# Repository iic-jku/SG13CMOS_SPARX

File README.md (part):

# SPARX: An Open-Source, Automated, Programmatically Generated, Frequency-Scalable Six-Port Receiver in 130-nm CMOS

(c) 2025-2026 Simon Dorrer, David Kellerer-Pirklbauer, and Harald Pretl

Institute for Integrated Circuits and Quantum Computing, Johannes Kepler University (JKU), Linz, Austria

> [!IMPORTANT]
> This repository requires the [IIC-OSIC-TOOLS](https://github.com/iic-jku/IIC-OSIC-TOOLS) container with tag `2026.11` or later.

> [!TIP]
> This repository is based on the [ihp-sg13g2-ams-chip-template](https://github.com/iic-jku/ihp-sg13g2-ams-chip-template) template repository and has been extended with electromagnetic (EM) simulations using the tool AWS Palace. For a better understanding of the folder structure, how to use the Makefiles, and how to implement your own designs, it is recommended to go through this [tutorial](https://iic-jku.github.io/ihp-sg13g2-ams-chip-template/index.html).

> [!NOTE]
> SPARX stands for **S**ix-**P**ort **A**utomated Receiver (**RX**). The name also carries a subtle double meaning: *SPARX* sounds like *spark*, which translates to *Funken* in German. Fittingly, the German verb *funken* also means to communicate via radio, a subtle nod to the wireless world this receiver was designed for.

<p align="center">
  
  <br>
  <em>Die photo of the ihp-sg13cmos six-port receiver for 160 GHz (1 × 1.4 mm²), taped out in March 2026.</em>
</p>

<p align="center">
  
  <br>
  <em>Chip render of the ihp-sg13cmos six-port receiver for 160 GHz with M5 GND plane and pinout (1 × 1.4 mm²).</em>
</p>

## Chip Specifications

| Parameter           | Value                                                                             |
| ------------------- | --------------------------------------------------------------------------------- |
| Technology          | IHP SG13CMOS (130 nm CMOS)                                                        |
| Die Area            | 1 × 1.4 mm²                                                                       |
| Supply Voltage      | 1.5 V                                                                             |

## Documentation

> [!IMPORTANT]
> This work has been published at the 2026 IEEE Nordic Circuits and Systems Conference (NorCAS) and is available in [IEEE Xplore](https://ieeexplore.ieee.org/document/11791174), doi: [10.1109/NorCAS71164.2026.11791174](https://doi.org/10.1109/NorCAS71164.2026.11791174). The preprint is available on [ResearchGate](https://www.researchgate.net/publication/418259168_SPARX_An_Open-Source_Automated_Programmatically_Generated_Frequency-Scalable_Six-Port_Receiver_in_130-nm_CMOS). [Cite This Work](#cite-this-work) gives the BibTeX entries.
>
> © 2026 IEEE. Personal use of this material is permitted. Permission from IEEE must be obtained for all other uses, in any current or future media, including reprinting/republishing this material for advertising or promotional purposes, creating new collective works, for resale or redistribution to servers or lists, or reuse of any copyrighted component of this work in other works.

The full documentation of SPARX is available [here](https://iic-jku.github.io/SG13CMOS_SPARX/index.html).

## Overview

The complete layout is generated in Python using self-made RF devices as a GDSFactory IHP PDK add-on. S-parameter simulation of the passive RF structures (BPF, WPD, and BLC) is performed with AWS Palace. The de-embedded EM results are then fitted to passivity-enforced lumped element models with [snp2le](https://github.com/iic-jku/snp2le), in both SPICE and Spectre dialects, and resimulated in Xschem testbenches with ngspice and VACASK. The six-port core is verified in two ways: as a single fitted model of the full-core EM simulation and as a composition of the individual BPF, WPD, and BLC models. With KLayout, Magic, and Netgen, a complete DRC, LVS, and PEX verification flow is implemented, and gdscheck adds a third DRC engine. The SBD-based power detector is designed in Xschem and simulated with ngspice and VACASK. This repository is controlled by a Makefile. Just clone it and run `make all` to build the six-port receiver at 160 GHz, verify it, run the EM simulations, extract the lumped element models, and simulate all testbenches. To generate a frequency-scalable layout at a different target frequency, for example 77 GHz, run `make build-layout FREQ=77`. A [regression](#regression) on every push to `main` exercises the complete tool flow in GitHub Actions inside the IIC-OSIC-TOOLS container. The following video demonstrates the generation of six-port receivers from 60 GHz to 300 GHz in under one minute.

**Index Terms:** Branch-line coupler, frequency-scalable layout, GDSFactory, hairpin coupled-line bandpass filter, IHP Open-PDK, mmWave, open-source EDA, power detector, programmatic layout, Schottky barrier diode, six-port receiver, Wilkinson power divider.

https://github.com/user-attachments/assets/a1e6cacb-4a70-4f2c-9b7a-f4b6fbb5a47a
<p align="center">
  <em>Generation of Six-Port Receivers from 60 GHz to 300 GHz.</em>
</p>

## References
To understand the principle of six-port receivers and their architectures, it is recommended to read the following references:
- A. Koelpin, G. Vinci, B. Laemmle, D. Kissinger and R. Weigel, "The Six-Port in Modern Society," in IEEE Microwave Magazine, vol. 11, no. 7, pp. 35-43, Dec. 2010, doi: 10.1109/MMM.2010.938584: https://ieeexplore.ieee.org/document/5590352
- T. Hentschel, "The six-port as a communications receiver," in IEEE Transactions on Microwave Theory and Techniques, vol. 53, no. 3, pp. 1039-1047, March 2005, doi: 10.1109/TMTT.2005.843507: https://ieeexplore.ieee.org/document/1406309
- M. Mailand, "System Analysis of Six-Port-Based RF-Receivers," in IEEE Transactions on Circuits and Systems I: Regular Papers, vol. 65, no. 1, pp. 319-330, Jan. 2018, doi: 10.1109/TCSI.2017.2734922: https://ieeexplore.ieee.org/document/8011483

## Requirements

To build this six-port receiver, the following tools and their respective dependencies are required:
- GDSFactory: https://github.com/gdsfactory/gdsfactory
- IHP Open-PDK GDSFactory Addon: https://github.com/iic-jku/IHP-GDSFactory-Addon
- IHP Open-PDK: https://github.com/iic-jku/IHP-Open-PDK
- snp2le (S-parameter to lumped element netlist conversion): https://github.com/iic-jku/snp2le, available on PyPI: https://pypi.org/project/snp2le/

GDSFactory, the IHP Open-PDK, and snp2le are already installed in the IIC-OSIC-TOOLS container.

The updated IHP Open-PDK GDSFactory version contains all self-made RF devices and wraps existing PCells provided by the IHP Open-PDK, allowing them to be used directly within the GDSFactory framework. We choose this approach because it requires very little maintenance. If IHP changes the layout of a cell, no wrapper update is necessary. Only interface changes to a PCell function require updates on our side.

## Block Diagram
- Six-Port
  - Branch Line Coupler (BLC)
  - Wilkinson Power Divider (WPD)
  - Hairpin Coupled-Line Bandpass Filter (BPF)
- Power Detector (PD)
  - Schottky Barrier Diode (SBD)
- Metal Stack
  - TopMetal2 (TM2): RF traces
  - Metal5 (M5): GND plane

<p align="center">
  
  <br>
  <em>Block diagram of the six-port receiver.</em>
</p>

## Schematic of SBD-based Power Detector

<p align="center">
  
  <br>
  <em>Schematic of the SBD-based power detector with replica circuit for fully-differential measurements. The supply and bias voltages are decoupled on-chip by MIM capacitors. The filtering capacitor is placed off-chip.</em>
</p>

## Design Flow

An overview of the open-source design flow for SPARX is shown below. The flow covers schematic entry, circuit simulation, parameterized layout generation, physical verification, post-layout simulation, EM simulation and resimulation of fitted lumped element models. All required tools and the IHP Open-PDK run inside the IIC-OSIC-TOOLS Docker image. The complete design flow is automated with Makefile targets, which are explained below.

<p align="center">
  
  <br>
  <em>Overview of the open-source design flow for SPARX.</em>
</p>

## Directory Structure

<details>
<summary>Show Directory Structure</summary>

```text
📁 SG13CMOS_SPARX/
├─ 📁 .github/
│  └─ 📁 workflows/
│     ├─ license-check.yml
│     ├─ quarto-publish.yml
│     └─ regression.yml
├─ 📁 doc/
│  ├─ 📁 fig/
│  ├─ 📁 videos/
│  ├─ _quarto.yml
│  ├─ index.qmd
│  ├─ requirements.txt
│  └─ Makefile
├─ 📁 LICENSES/
│  ├─ Apache-2.0.txt
│  └─ SHL-2.1.txt
├─ 📁 layout/
│  ├─ sparx60_top.gds
│  ├─ ...
│  ├─ sparx160_top.gds
│  ├─ ...
│  ├─ sparx300_top.gds
│  └─ sparx_powdet_sbd.gds
├─ 📁 measurements/
├─ 📁 netlist/
│  ├─ 📁 layout/
│  │  ├─ sparx_powdet_sbd_klayout.cir
│  │  └─ sparx_powdet_sbd_magic.ext.spc
│  ├─ 📁 pex/
│  │  ├─ sparx_powdet_sbd_klayout_pex_3.spice
│  │  └─ sparx_powdet_sbd_magic_pex_3.spice
│  ├─ 📁 schematic/
│  │  ├─ sparx_powdet_sbd_klayout.cdl
│  │  └─ sparx_powdet_sbd_magic.spice
│  ├─ 📁 spectre/
│  │  ├─ sparx_blc_le.inc
│  │  ├─ sparx_bpf_le.inc
│  │  ├─ sparx_core_le.inc
│  │  └─ sparx_wpd_le.inc
│  └─ 📁 spice/
│     ├─ sparx_blc_le.spice
│     ├─ sparx_bpf_le.spice
│     ├─ sparx_core_le.spice
│     └─ sparx_wpd_le.spice
├─ 📁 release/
│  ├─ 📁 v.1.0.0/
│  │  ├─ 📁 gds/
│  │  ├─ 📁 img/
│  │  └─ ReleaseNote.md
│  └─ 📁 v.2.0.0/
│     ├─ 📁 gds/
│     ├─ 📁 img/
│     └─ 📁 netlist/
├─ 📁 render/
│  ├─ 📁 blender/
│  └─ 📁 img/
│     ├─ sparx160_top_black.png
│     ├─ sparx160_top_black_TM2.png
│     └─ sparx160_top_white.png
├─ 📁 schematic/
│  └─ 📁 xschem/
│     ├─ sparx_blc_le.sym
│     ├─ sparx_bpf_le.sym
│     ├─ sparx_core.sch
│     ├─ sparx_core.sym
│     ├─ sparx_core_le.sym
│     ├─ sparx_powdet_sbd.sch
│     ├─ sparx_powdet_sbd.sym
│     ├─ sparx_powdet_sbd_pex.sym
│     ├─ sparx_top.sch
│     ├─ sparx_top.sym
│     ├─ sparx_top_le.sch
│     ├─ sparx_top_le.sym
│     ├─ sparx_top_lvs.sch
│     ├─ sparx_wpd_le.sym
│     └─ xschemrc
├─ 📁 scripts/
│  ├─ 📁 assets/
│  ├─ check_pex_ports.py
│  ├─ img2lay.py
│  ├─ prune_pex_symbol.py
│  ├─ six_port_gen.py
│  └─ sparx_powdet_sbd_circuit.ipynb
├─ 📁 sscs-ose-code-a-chip/
│  ├─ 📁 assets/
│  ├─ README.md
│  └─ SPARX_JKU_ISSCC2027.ipynb
├─ 📁 testbenches/
│  └─ 📁 xschem/
│     ├─ 📁 plot_simulations/
│     │  ├─ 📁 data/
│     │  ├─ 📁 figures/
│     │  ├─ check_sparx_powdet_sbd_tb_acsp_ngspice.py
│     │  ├─ ngspice2python.py
│     │  ├─ plot_n_port_tb_acsp_ngspice.py
│     │  ├─ plot_n_port_tb_acsp_vacask.py
│     │  ├─ plot_n_port_tb_tran_ngspice.py
│     │  ├─ plot_sparx_powdet_sbd_tb_hb_V-W_vacask.py
│     │  ├─ plot_sparx_powdet_sbd_tb_hb_dBV-dBV_vacask.py
│     │  ├─ plot_sparx_powdet_sbd_tb_nf_vacask.py
│     │  ├─ plot_sparx_powdet_sbd_tb_pss_vacask.py
│     │  ├─ plot_sparx_powdet_sbd_tb_tn_lo_vacask.py
│     │  ├─ plot_sparx_powdet_sbd_tb_tn_vacask.py
│     │  ├─ plot_sparx_top_le_tb_nf_vacask.py
│     │  ├─ plot_sparx_top_le_tb_rx_vacask.py
│     │  ├─ plot_sparx_top_le_tb_tn_vacask.py
│     │  └─ sparam_plot.py
│     ├─ sparx_blc_le_tb_acsp_ngspice.sch
│     ├─ ...
│     ├─ sparx_core_tb_acsp_ngspice.sch
│     ├─ ...
│     ├─ sparx_powdet_sbd_tb_acsp_ngspice.sch
│     ├─ ...
│     ├─ sparx_powdet_sbd_tb_ngspice.sch
│     ├─ ...
│     ├─ sparx_top_le_tb_nf_vacask.sch
│     ├─ sparx_top_le_tb_rx_vacask.sch
│     ├─ sparx_top_le_tb_tn_vacask.sch
│     ├─ sparx_top_le_tb_tran_ngspice.sch
│     ├─ sparx_top_tb_tran_ngspice.sch
│     ├─ sim_range.inc
│     ├─ sim_range.spice
│     └─ xschemrc
├─ 📁 verification/
│  ├─ 📁 drc/
│  │  ├─ 📁 sparx160_top.klayout.drc/
│  │  ├─ 📁 sparx160_top.magic.drc/
│  │  ├─ 📁 sparx_powdet_sbd.klayout.drc/
│  │  └─ 📁 sparx_powdet_sbd.magic.drc/
│  ├─ 📁 em/
│  │  ├─ 📁 layout/
│  │  ├─ 📁 metal_model/
│  │  ├─ 📁 palace_model/
│  │  ├─ 📁 s-parameter/
│  │  ├─ 📁 scripts/
│  │  └─ 📁 stackups/
│  └─ 📁 lvs/
│     ├─ 📁 sparx_powdet_sbd.klayout.lvs/
│     └─ 📁 sparx_powdet_sbd.magic.lvs/
├─ .gitattributes
├─ .gitignore
├─ CITATION.cff
├─ KNOWN_ISSUES.md
├─ LICENSE
├─ Makefile
├─ README.md
└─ REUSE.toml
```

</details>

## Xschem Configuration

Xschem reads exactly one `xschemrc` at start-up, and that file decides which symbol libraries are visible and where netlists and simulation output are written. This repository ships one per folder that holds schematics:

| `xschemrc` | Belongs to |
| --- | --- |
| [`schematic/xschem/xschemrc`](schematic/xschem/xschemrc) | the six-port and power detector schematics and symbols |
| [`testbenches/xschem/xschemrc`](testbenches/xschem/xschemrc) | the ngspice and VACASK testbenches |

### What Every File Does

Both run the same four steps, in this order:

1. **Pick the PDK.** `PDK_ROOT` is probed in the usual install locations if the environment does not set it, and `PDK` falls back to `ihp-sg13g2`. The container already exports `PDK_ROOT`, and [`.designinit`](.designinit) exports `PDK`, so this step is only a safety net for an Xschem started outside that environment.
2. **Source the PDK `xschemrc`.** `$PDK_ROOT/$PDK/libs.tech/xschem/xschemrc` brings in the IHP device symbols, the ngspice and VACASK model paths and the IHP menu. It is guarded by `[info exists PDK]` so it is read once even when the two project files are chained.
3. **Add the project library paths.** `append_xschem_library_path_unique` appends a folder to `XSCHEM_LIBRARY_PATH` only if it is not already there, so the same folder never appears twice no matter how the files are chained. [`schematic/xschem/xschemrc`](schematic/xschem/xschemrc) puts itself and `testbenches/xschem/` on the path. [`testbenches/xschem/xschemrc`](testbenches/xschem/xschemrc) adds none of its own and gets both from the file it sources.
4. **Pin the netlist directory.** `pin_netlist_dir` decides where `xschem netlist` and the simulators write.

Both helper procedures are defined behind an `[info commands ...]` guard, so sourcing one file from the other is harmless and the order does not matter.

### How the Files Are Chained

The testbench file pulls in the schematic file:

```text
testbenches/xschem/xschemrc
└─ source schematic/xschem/xschemrc
```

Either file therefore sees both folders, which is what lets a testbench instantiate `sparx_powdet_sbd.sym` or one of the `sparx_*_le.sym` lumped element symbols, and what lets you open a testbench from a session started in `schematic/xschem/`.

### Where Netlists and Simulation Output Go

`pin_netlist_dir` maps the folder of the schematic being netlisted to a `simulations/` folder:

| Schematic lives in | `netlist_dir` |
| --- | --- |
| `testbenches/xschem` | `testbenches/xschem/simulations` |
| `schematic/xschem` | `testbenches/xschem/simulations` |
| anywhere else (a PDK example) | left at the value the `xschemrc` pinned |

It runs twice: once while the `xschemrc` is read, using that file's own folder, and again through Xschem's `load_file_postprocess` hook for every schematic that is opened afterwards. The second call keeps the netlist next to its own schematic tree no matter where the session was started, so the relative includes of the testbenches, such as `.include ../../../netlist/spice/sparx_bpf_le.spice` or `.include ../../../netlist/pex/sparx_powdet_sbd_magic_pex_3.spice`, always resolve from `testbenches/xschem/simulations/`.

A `set netlist_dir` passed on the Xschem command line still wins, because `--command` runs after the file is loaded. The LVS netlist targets rely on this to write into `netlist/schematic/`, and `sim-xschem` to write into `testbenches/xschem/simulations/`.

Both `simulations/` folders are generated and git-ignored.

### Which File Is Used

- The Makefile targets always name one explicitly with `--rcfile`, so a target behaves the same from any working directory.
- Starting Xschem from within one of the two folders picks up that folder's file, which is the normal interactive case.
- `make open` starts Xschem in the file's own directory, so the same rule applies to every button of the file browser, see [Open the Design Files](#open-the-design-files).

## Makefile Structure

The whole flow is driven by the single top-level `Makefile`, and [Makefile Targets](#makefile-targets) below documents each target. The figure below shows how the targets are connected when you run `make all`.

<p align="center">
  
  <br>
  <em>Overview of the Makefile targets.</em>
</p>

Every coloured branch is one stage of the flow, and its header names the folders the stage writes to. The numbers in the headers give the execution order of `make all`, and inside a branch the targets run from top to bottom.

All targets live in the one `Makefile`, so every arrow is a direct `$(MAKE) <target>` call. The boxes directly below a header are called by `make all` itself, and an indented box is called by the nearest box above it with less indent. A box with a thicker border calls the boxes indented below it. The second line of a box shows the parameters of the call, where `*` stands for any part of a testbench name, and in `sparx*_top` for the design frequency. A box marked ×N stands for N calls of the same target, for example one SPICE and one Spectre fit per `snp2le` box, and a box that names two targets calls each of them once. The dashed boxes with a `WITH_CORE=1` tag run only with `make all WITH_CORE=1`, see below. The figure leaves out the helper steps. `copy-sparam` copies the Touchstone files of each EM run to `verification/em/s-parameter/`, `klayout-lvs` and `magic-lvs` first export the schematic netlist with `klayout-lvs-netlist` and `magic-lvs-netlist`, and `klayout-pex` and `magic-pex` first regenerate the PEX symbol with `symbol-pex`.

At the top level, `make all` runs five stages in this order:

1. **Layout**: `build-top` installs the GDSFactory PDK add-on (`build-pdk`), generates the 160 GHz layout together with the EM structures in `verification/em/layout/` (`build-layout`), and renders the top-level GDS (`render-gds`).
2. **Verification**: `klayout-verify` runs DRC, LVS and PEX of the SBD power detector `sparx_powdet_sbd`, `gdscheck-drc` its gdscheck DRC, and `magic-verify` its LVS and PEX. Then `klayout-drc` and `gdscheck-drc` (both `DRC_LEVEL=macro`) check the top cell of the design frequency, `sparx160_top` by default and `sparx<FREQ>_top` with `FREQ=<GHz>`. The figure already shows the LVS of the top cell (`klayout-lvs`, `magic-lvs`), which `make all` does not run yet: it follows once top-level LVS works, see [`ToDo.md`](ToDo.md).
3. **EM simulation**: AWS Palace solves the BPF, WPD and BLC (`sim-bpf-em`, `sim-wpd-em`, `sim-blc-em`), and `copy-sparam` copies the raw and de-embedded Touchstone files of each run to `verification/em/s-parameter/`.
4. **LE models**: `snp2le` fits the raw Touchstone file of each block to a SPICE and a Spectre lumped element netlist, with the fit orders 13 (BPF), 10 (WPD) and 6 (BLC).
5. **Circuit simulation**: `sim-all` runs 22 of the 25 testbenches, all except the three transients of the passive LE models. With the power-detector design variants (`sim-powdet-variants`) and the post-layout runs of the receiver benches, these are 31 simulations.

The simulations run last, so the block benches and the composed-core benches use the LE models that the same invocation has just fitted.

The dashed boxes are the full six-port core: its EM solve (`sim-sparx-core-em`) and its fit with `ORDER=24` and the core's thermal noise (`LE_NOISE=thermal`). `make all` runs them only with `WITH_CORE=1`, because the seven-port EM solve takes about 20 times the core-hours of the three blocks, and the committed run needed 119 GB of memory on 128 MPI ranks. It runs them through `make sparx-core` as one step after the block fits. That step also copies the core's Touchstone files and runs the two `sparx_core_tb_acsp_*` benches, which `sim-all` then repeats. With the default `WITH_CORE=0`, `make all` simulates the committed full-core fit, `netlist/spice/sparx_core_le.spice` and `netlist/spectre/sparx_core_le.inc`, in the `sparx_core_le_tb_acsp_*` and `sparx_top_le_tb_*` benches.

> [!IMPORTANT]
> After a change to a structure parameter in `scripts/six_port_gen.py`, run `make sparx-core` or `make all WITH_CORE=1`. Otherwise the full-core benches (`sparx_core_le_tb_acsp_*`, `sparx_top_le_tb_*`) keep simulating the core fit of the old layout, and nothing warns about it.

`make regression` runs a short subset of these stages as a tool and flow smoke test, see [Regression](#regression).

## Makefile Targets

### Show Available Targets

The default Make target is `help`, so running `make` prints usage and all available targets with short descriptions.

```sh
make
make help
```

### PDK Guard

Every target except `help` and `clean` needs the `ihp-sg13g2` PDK. A wrong `$PDK`, for example `ihp-sg13cmos5l`, silently mixes technologies: DRC and LVS run against the wrong rule deck, Magic reads the wrong `magicrc`, `kpex` is handed the wrong `--pdk`, and the EM flow reads its process stackup from `$PDK_ROOT/$PDK/libs.tech/palace/`. The Makefile therefore compares `$PDK` against `REQUIRED_PDK` once when it is parsed, before any target runs:

```sh
$ sak-pdk ihp-sg13cmos5l
$ make klayout-drc
Makefile:25: *** PDK is "ihp-sg13cmos5l", but this chip needs "ihp-sg13g2". Run `sak-pdk ihp-sg13g2` in this shell and retry, or pass REQUIRED_PDK= to skip this check.  Stop.
```

The check is a parse-time conditional at the top of the Makefile, not a prerequisite of each target, so it costs nothing and cannot be forgotten when a target is added. `help` and `clean` are exempt, so the usage text and the cleanup still work under any PDK. `open` is not exempt: it launches Xschem, KLayout and Magic, which all read the selected PDK.

Switch the PDK with `sak-pdk ihp-sg13g2`, which also sets `PDKPATH`, `KLAYOUT_PATH`, `SPICE_USERINIT_DIR` and `STD_CELL_LIBRARY`. To run a single target against another PDK anyway, pass an empty `REQUIRED_PDK`:

```sh
make <target> REQUIRED_PDK=          # skip the check
make <target> REQUIRED_PDK=<pdk>     # require a different PDK
```

### Open the Design Files

Opens a file browser for this folder with `sak-open.py` from the [IIC-OSIC-TOOLS](https://github.com/iic-jku/IIC-OSIC-TOOLS), one button per design file, grouped by directory:

```sh
make open
```

All file types are ticked at startup, each checkbox showing how many files of that type the tree holds. `None` and `All` untick or tick every type at once, and `Rescan` rereads the tree immediately. The filter field keeps only the files whose path contains the typed text (case-insensitive), so `powdet` reduces the list to the files of the power detector and its testbenches. Clicking a directory heading folds it away. Hovering a button shows the file's size and age in the status line at the bottom. A right click on a button opens a menu with `Cell view` (all views of that cell, for example its `.sch`, `.sym` and `.gds`, wherever they live in the tree), `Scope here` (rescan from that file's directory), `Fold all`, `Save view` (remember the folded directories and ticked types for this tree), `Open shell` and `Copy path`.

Clicking a button launches the matching tool in the file's own directory, so Xschem finds its `simulations/` folder and KLayout the layouts where they belong:

| File type | Tool |
| --- | --- |
| `.sch`, `.sym` | Xschem |
| `.gds`, `.gds.gz`, `.oas`, `.oas.gz` | KLayout in edit mode |
| `.mag` | Magic |
| `.vcd`, `.fst`, `.gtkw` | GTKWave |
| `.raw` | gaw (ngspice rawfile) |
| `.png`, `.pdf` | the desktop's handler (`xdg-open`) |
| `.sv`, `.svh`, `.v`, `.vh`, `.vhd`, `.vhdl`, `.spice`, `.cir`, `.sp`, `.cdl`, `.sdc`, `.lef`, `.lib`, `.tcl`, `.mk`, `.yaml`, `.json`, `.py`, `.qmd`, `.tex`, `.md` and `Makefile` | gvim |

Only these types get a button. Files with any other extension (`.sh`, `.svg`, `.save`, `.inc`, `.sNp`, `.txt`, `.csv` and so on) are not listed.

Schematics and symbols that belong to one design unit share a single tabbed Xschem instance instead of one process per click. The unit is the nearest ancestor holding a `Makefile`, so the whole design is one unit and the documentation under [`doc/`](doc/) another. Every tab then writes its netlists to the folder the `xschemrc` pins, see [Xschem Configuration](#xschem-configuration).

The tree is rescanned every 15 s, so files a running flow produces appear on their own and are highlighted for a minute. Generated directories are skipped by default: `runs/`, `sim_build/`, `obj_dir/`, `simulations/`, `__pycache__/`, `_freeze/` and `.git/`. The Xschem `simulations/` folder is one of them, so the `.raw` files show up only with `--all`. Pass extra options with `OPEN_ARGS`:

```sh
make open OPEN_ARGS=--all                      # include the simulation outputs
make open OPEN_ARGS="--prune palace_model"     # skip one more directory name
```

At most 400 buttons are drawn at once, because each one is an X window, and what is left out is stated at the end of the list. That cap is easy to hit with `--all`, which also pulls in the Palace meshes under `verification/em/palace_model/` and every simulation output, so narrow it with `--prune` rather than scrolling. The same target exists in [`doc/`](doc/) for the documentation sources and figures.

> [!NOTE]
> This target needs a display. Run it inside the container's VNC/noVNC desktop or over X11 forwarding. In a shell-only container it stops with `cannot open a window`. The `.png` and `.pdf` buttons hand the file to the desktop's registered handler, so those two need the full VNC/noVNC session and do not work over a bare X forward.

### Build PDK

Clones and installs the GDSFactory PDK add-on (`IHP-GDSFactory-Addon`):

```sh
make build-pdk
```

### Build SPARX Layout

Generates the six-port layout GDS files for a specific frequency (e.g. `layout/sparx160_top.gds` and `layout/sparx_powdet_sbd.gds` for the default 160 GHz, or `layout/sparx77_top.gds` and `layout/sparx_powdet_sbd.gds` for 77 GHz) by calling `six_port_gen.py`:

```sh
make build-layout
make build-layout FREQ=77
make build-layout FREQ=77 NO_FILL=1
make build-layout FREQ=77 NO_FILL_M5=1
```

The `FREQ` parameter sets the design frequency in GHz (default: `160`). `NO_FILL=1` disables metal fill (faster for layout preview). `NO_FILL_M5=1` disables only the Metal5 ground fill.

> [!NOTE]
> `build-layout` also writes the EM sub-structures of the design (BLC, WPD, BPF, and the blank six-port core, each with the Palace port markers on layers 201..207) to `verification/em/layout/`. The EM simulation targets solve exactly these files, so the EM results always match the structures instantiated in the top-level layout.

### Build Frequency Sweep Automatically

Builds a frequency sweep by repeatedly calling `build-layout` for each frequency from `START_FREQ` to `STOP_FREQ` using `STEP_FREQ`.

```sh
make build-layout-sweep
make build-layout-sweep START_FREQ=60 STOP_FREQ=300 STEP_FREQ=20
make build-layout-sweep START_FREQ=60 STOP_FREQ=300 STEP_FREQ=20 NO_FILL=1
make build-layout-sweep START_FREQ=60 STOP_FREQ=300 STEP_FREQ=20 NO_FILL_M5=1
```

Default sweep settings are `START_FREQ=60`, `STOP_FREQ=300`, and `STEP_FREQ=20` (all in GHz). `NO_FILL` and `NO_FILL_M5` are forwarded to each `build-layout` run.

All thirteen layouts of the default sweep pass the KLayout DRC at `macro` level, and their EM simulations are clean as well. The repository commits the DRC reports, the EM results and the fitted models of 160 GHz only. Any other frequency reruns the same targets with `FREQ=<GHz>`, for example `make klayout-drc FREQ=80` and `make sim-bpf-em FREQ=80`.

### Build Top Cell

Builds the top-level cell by running `build-pdk`, `build-layout`, and `render-gds`:

```sh
make build-top
```

### Render Top Layout

Renders the top-level GDS `layout/sparx<FREQ>_top.gds` with `sak-render.py` from the [IIC-OSIC-TOOLS](https://github.com/iic-jku/IIC-OSIC-TOOLS):

```sh
make render-gds
make render-gds FREQ=77
```

Three images are written to the `render/img/` folder:

- `sparx<FREQ>_top_white.png` and `sparx<FREQ>_top_black.png`: all physical mask layers, on a white and on a black background.
- `sparx<FREQ>_top_black_TM2.png`: only `TopMetal2`, `TopVia2`, the `TopMetal2` filler and `Passiv` on a black background, which shows the six-port RF structures and the pads without the Metal5 ground plane underneath.

All three images are 2048 px wide and rendered with 4x oversampling. `sak-render.py` reads the layer colours from the PDK's own KLayout layer properties and crops to the drawn geometry, so the images have no border margin.

### Design Rule Check (DRC)

Runs DRC on the GDS layout in `layout/`. All three flows use `sak-drc.sh` and write their reports into per-cell run folders: `verification/drc/<CELL>.magic.drc/` (Magic), `verification/drc/<CELL>.klayout.drc/` (KLayout, `.lyrdb`) and `verification/drc/<CELL>.gdscheck.drc/` (gdscheck, `.lyrdb`). The run folders are wiped at the start of each run, so they always reflect the latest run only.

The `DRC_LEVEL` parameter selects the KLayout DRC level and the gdscheck suite (`sak-drc.sh -l`). It is ignored by `magic-drc`, since Magic has no selectable rule decks and always runs the full rule set compiled into the PDK's Magic tech file:

- `precheck` = the foundry precheck rule set and the pin checks (fast iteration)
- `macro` = block-in-isolation sign-off: the full FEOL and BEOL rules with off-grid, angle, recommended and pin checks, without chip-level density, the extra rules and antenna (default)
- `regular` = full-chip sign-off: all checks, including density, the extra rules and antenna

For the IHP Open-PDK, `sak-drc.sh` passes `--precheck_drc --no_density --no_offgrid --no_angle --disable_extra_rules --no_recommended` for `precheck`, `--no_density --disable_extra_rules` for `macro` and `--antenna` for `regular` to the PDK's `run_drc.py`, which adds the pin checks at every level:

| Check | `precheck` | `macro` _(default)_ | `regular` |
| --- | :---: | :---: | :---: |
| Foundry precheck rule set | ✓ | ✓ | ✓ |
| Pin / label | ✓ | ✓ | ✓ |
| Full FEOL + BEOL rules | – | ✓ | ✓ |
| Off-grid / angle | – | ✓ | ✓ |
| Recommended rules | – | ✓ | ✓ |
| Extra rules | – | – | ✓ |
| Density (full-chip fill) | – | – | ✓ |
| Antenna | – | – | ✓ |

The `DRC_JOBS` parameter (`sak-drc.sh -j`) sets how many jobs one run uses at most. The default is 4, or the CPU count if lower, for KLayout and every CPU the container may use for gdscheck, which runs as one process with that many threads. Up to 4 jobs, `precheck` and `macro` run as one KLayout process with that many threads, and `regular` runs its four rule sets (main, extra rules, density and antenna) as parallel processes and writes the reports of the last three into the subfolders `maximal/`, `density/` and `antenna/` of the run folder. Above 4, `run_drc.py` splits the rule deck into its tables, one process each, and merges their reports into one. Every KLayout process needs about 0.5 GiB of RAM plus the layout, so this only pays off for large layouts.

**KLayout DRC (regular)** runs a full (`regular`) KLayout DRC on the top-level cell:

```sh
make klayout-drc-regular
```

**KLayout DRC** runs a KLayout DRC at the selected `DRC_LEVEL`. `CELL` defaults to the top cell of the design frequency, `sparx<FREQ>_top`:

```sh
make klayout-drc
make klayout-drc FREQ=80
make klayout-drc CELL=sparx_powdet_sbd
make klayout-drc CELL=sparx_powdet_sbd DRC_LEVEL=regular
```

**Magic DRC** runs Magic's full DRC on the layout (`sak-drc.sh -m`), hierarchically and without flattening any cell:

```sh
make magic-drc
make magic-drc FREQ=80
make magic-drc CELL=sparx_powdet_sbd
```

**gdscheck DRC** runs [gdscheck](https://github.com/aesc-silicon/gdscheck) (`sak-drc.sh -g`), a standalone DRC engine with its own IHP rule decks built into the binary. The DRC levels map onto its suites: `precheck` runs `precheck` (IHP's open-source precheck subset, which includes the density rules, so a single macro fails it), `macro` runs `core` (all geometric rules without density and antenna) and `regular` runs `main` (all rules, density and antenna included). The `GDSCHECK_SUITE` parameter (`sak-drc.sh -s`) replaces this mapping and also reaches the suites `density`, `antenna` and `recommended` (the advisory rules whose names end in `R`, not part of `main`). `gdscheck list-suites --process ihp-sg13g2` lists them. The `GDSCHECK_DECKS` parameter (`sak-drc.sh -D`) runs single rule decks instead of a suite, comma-separated, and `gdscheck list-decks --process ihp-sg13g2` lists them. It cannot be combined with `GDSCHECK_SUITE`. The IHP layer decks include their fill and density rules, so a single cell can fail a deck run on a rule that `macro` does not check.

**gdscheck DRC (regular)** runs the `main` suite on the top-level cell:

```sh
make gdscheck-drc-regular
```

**gdscheck DRC** runs gdscheck at the selected `DRC_LEVEL`, `GDSCHECK_SUITE` or `GDSCHECK_DECKS`. `CELL` defaults to the top cell of the design frequency, `sparx<FREQ>_top`:

```sh
make gdscheck-drc
make gdscheck-drc FREQ=80
make gdscheck-drc CELL=sparx_powdet_sbd
make gdscheck-drc CELL=sparx_powdet_sbd GDSCHECK_DECKS=cont,via1
```

> [!NOTE]
> KLayout is the sign-off DRC. Magic and gdscheck give a second and a third opinion, and on `sparx160_top` only KLayout passes at `macro` level. See [`KNOWN_ISSUES.md`](KNOWN_ISSUES.md) for the full breakdown:
>
> - `make klayout-drc` (`macro` level) is clean. `make klayout-drc-regular` reports antenna violations that were waived by IHP for the tapeout.
> - `make gdscheck-drc` reports `nSDB.e` on the contact of IHP's `schottky` PCell, which the KLayout deck leaves out of the rule. `make gdscheck-drc-regular` also reports the antenna rules.
> - `make magic-drc` reports `MIM.e` and `MIM.i`. KLayout reports no `MIM.e`, and `MIM.i` is in no KLayout deck.
>
> A flow stops on a violation of any engine it calls, so the flows leave the Magic DRC out until `MIM.e` and `MIM.i` are settled upstream: its lines are commented out in `magic-verify` and in `make all`, and `magic-drc` still runs it on its own. gdscheck stays in, so until `nSDB.e` is fixed it stops `make all` at `sparx_powdet_sbd`. To continue meanwhile, run the later steps directly. Upstream calls gdscheck experimental, so a clean gdscheck run is no sign-off on its own.

### Export Schematic Netlist for LVS

Exports the schematic netlist for LVS from Xschem and places it in `netlist/schematic/`.

The `EV_PRECISION` parameter sets the number of significant digits used by Xschem's `ev` function when calculating device properties (default: 5). Increase this to avoid LVS mismatches caused by floating-point rounding differences between Xschem and KLayout (see [xschem#465](https://github.com/StefanSchippers/xschem/issues/465)).

The `ntap` and `ptap` substrate contacts are ignored during LVS in both flows. `sak-lvs.sh` runs KLayout LVS with the `--disable_tap_extraction` option so it does not extract `ntap` and `ptap` devices from the layout (matching Magic + Netgen LVS).

KLayout uses CDL netlists, while Magic uses SPICE netlists. Accordingly, `klayout-lvs-netlist` uses the Xschem commands `set spiceprefix 1`, `set lvs_netlist 1`, `set top_is_subckt 1`, and `set lvs_ignore 1`, while `magic-lvs-netlist` uses `set spiceprefix 1`, `set lvs_netlist 0`, `set top_is_subckt 1`, and `set lvs_ignore 1`. Hence, switching between CDL and SPICE netlists can be done with `lvs_netlist`.

To extract a CDL schematic netlist for KLayout LVS, use the following target:
```sh
make klayout-lvs-netlist
make klayout-lvs-netlist CELL=sparx_powdet_sbd
make klayout-lvs-netlist EV_PRECISION=5
```

To extract a SPICE schematic netlist for Magic + Netgen LVS, use the following target:
```sh
make magic-lvs-netlist
make magic-lvs-netlist CELL=sparx_powdet_sbd
make magic-lvs-netlist EV_PRECISION=5
```

### Layout Versus Schematic (LVS)

Exports the schematic netlist from Xschem, then runs LVS. Compares the GDS layout in `layout/` against the schematic netlist in `netlist/schematic/`. Both flows use `sak-lvs.sh` and write their reports into per-cell run folders: `verification/lvs/<CELL>.magic.lvs/` (Magic + Netgen) and `verification/lvs/<CELL>.klayout.lvs/` (KLayout, `.lvsdb`). The run folders are wiped at the start of each run, so they always reflect the latest run only. The extracted layout netlist is moved to `netlist/layout/`.

**KLayout LVS** uses `sak-lvs.sh` (KLayout mode `-k`), which wraps `run_lvs.py` from the IHP Open-PDK:

```sh
make klayout-lvs
make klayout-lvs CELL=sparx_powdet_sbd
```

**Magic + Netgen LVS** uses `sak-lvs.sh` (Magic + Netgen mode `-m`, the default), which extracts the layout netlist with Magic and compares it against the schematic netlist with Netgen, using the Netgen setup from the IHP Open-PDK:

```sh
make magic-lvs
make magic-lvs CELL=sparx_powdet_sbd
```

### Build Xschem PEX Symbol

Builds the Xschem symbol the PEX flow needs, `schematic/xschem/<CELL>_pex.sym`, from the regular cell symbol `schematic/xschem/<CELL>.sym`:

```sh
make symbol-pex CELL=sparx_powdet_sbd
```

The generated symbol is a copy of `<CELL>.sym` with two changes: `type=subcircuit` becomes `type=primitive`, and the pin boxes the extracted netlist has no port for are dropped. Everything else (the remaining pin boxes and their order, every text label, `format`, `spectre_format`, `template`, graphics) is inherited, which is exactly what the PEX flow needs:

- **`type=primitive`** stops Xschem from descending into a schematic of the same name. There is no `<CELL>_pex.sch`, so the instance line is emitted as it stands and the subcircuit comes from the `.include`d PEX netlist instead.
- **`format="@name @pinlist @symname"`** makes the instance reference `@symname`, which resolves to `<CELL>_pex`, exactly the `.subckt` name the PEX flow writes.
- **The pin order** is what `sak-pin-reorder.py` reorders the extracted netlist to, so it has to be that of the cell symbol.

`PEX_MERGED_PINS` names the supply pins that the extraction does not report as ports of their own. It is empty by default: the power detector keeps `vdd` and `vss` as separate ports in both the Magic and the KPEX extraction, so nothing is dropped and `sparx_powdet_sbd_pex.sym` carries the same five pins as `sparx_powdet_sbd.sym`. Set it for a cell whose supplies come out of the flat extraction as one node, for example two ground pins that both tap the substrate: `make magic-pex CELL=<cellname> PEX_MERGED_PINS="<pin> ..."`.

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
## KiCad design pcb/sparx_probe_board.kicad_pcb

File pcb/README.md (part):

# SPARX probe board

KiCad 10 project of the board that carries a SPARX die on the wafer prober.
The die is glued onto the board and gold ball bonded at its top and bottom pad rows. LO and RF are probed from the left and the right with GSG probes. The four power detectors are read out with a differential probe on the board or through edge SMAs.

## Files

| File | Contents |
| --- | --- |
| `sparx_probe_board.kicad_pro` | Project: net classes (`DIE`, `RF_50`, `Power`), design rules, track and via presets |
| `sparx_probe_board.kicad_sch` | Root sheet: die, supply, VDD decoupling, DC monitor headers, mechanics |
| `detector.kicad_sch` | Readout of one detector, instantiated four times as `Detector 1` to `Detector 4` |
| `sparx_probe_board.kicad_pcb` | Board, revision 0.1 |
| `sparx_probe_board.kicad_dru` | Custom rules: the stricter value of JLCPCB and Aisler per rule, plus house rules |
| `lib/` | Project symbols, footprints (parts and the board-only logos) and the 3D models of the die with its bond wires and of the tip jacks |
| `render/` | Renders of the board |

Stock parts use the KiCad 10 libraries, and their 3D models resolve through `${KICAD10_3DMODEL_DIR}`. The SMA footprint is KiCad's `SMA_Molex_73251-1153_EdgeMount_Horizontal` with the changes listed in its description.

## Die and bond area

| Item | Value |
| --- | --- |
| Die | 1.05 × 1.35 × 0.2 mm, pads 2 × 7 at 125 µm pitch with 80.8 µm openings |
| Pad rows | `REF OUT VSS VDD VSS OUT REF`, pad 1 top left, detectors 1 to 4 top left, top right, bottom left, bottom right |
| Die land | 1.25 × 1.55 mm of `GND` copper inside a 3.2 × 4.6 mm solder mask window |
| Bond fingers | One row, 0.125 × 0.40 mm, 1.10 to 1.50 mm from the die centre: `OUT` at x ±0.27 mm, `VDD` at 0, `REF` fanned out to ±0.60 mm |
| `VSS` | Pads 3, 5, 10 and 12 bonded down onto 0.125 × 0.25 mm tongues of the land, stitch 0.90 mm from the die centre |
| Wire length (planar, to a landing 1.20 mm from the die centre) | `OUT` and `VDD` 0.63 mm, `REF` 0.67 mm, `VSS` 0.33 mm |

Wire length hardly matters below 2 GHz IF: 0.8 nH against 1.2 nH on `OUT` moves the detector response by 0.4 dB at 2 GHz.

Gold ball bonding on ENIG is marginal. Neither fab offers ENEPIG or soft gold, and Aisler's ENIG carries 0.05 to 0.1 µm of gold. Pull-test on the 5 × 5 mm bond test pad `TP1` first, and use ball-stitch-on-ball if the stitch does not hold.

## Probing

LO comes from the left and RF from the right, both GSG at 125 µm pitch. The RF pads sit 0.117 mm above the LO axis.
The board is laid out for GGB Picoprobe 170-GSG-100-BT-M probes (110 to 170 GHz, WR-6, 100 µm pitch). Their ground tips land about 33 µm inside the inner edge of the 125 µm ground pads.
The probe body, read off GGB's drawing `mod170.pdf`, is a block 30.5 mm wide from about 20 mm behind the tip, its bottom 1.2 mm above the tip, with a mounting plate 8.4 mm above the tip at the back. Every part within 1 mm of that outline (0.3 mm along the coaxial tip) stays below it:

| Parts under or beside the probe | Clearance |
| --- | --- |
| 0603 DC blocks `Ck04` (beside the block, not under it) | 0.51 mm |
| 0603 REF taps and links | 0.91 mm |
| Tip jacks, under the mounting plate | 3.7 mm |
| `D1`, under the mounting plate | 7.6 mm |

The DC monitor headers sit in the bottom corners, outside the probe footprint. Screw heads in `H1` to `H4`, under the mounting plates, must stay below 7 mm.

The LO pad wants about +12 dBm, which puts about −6 dBm on each detector, so the LO source needs the higher output power: about +9 dBm from an R&S ZTXR170 on LO, against −15 to −10 dBm from an OML V06VNA2 extender, which suits RF.

## Detector readout

Sheet `detector.kicad_sch`. The first digit of a reference is the detector, for example `R103` belongs to detector 1.

| Reference | Part | Default | Function |
| --- | --- | --- | --- |
| `Ck01`, `Ck02` | 2.7 pF C0G 0402 | fitted | Off-chip filter capacitor of `OUT` and `REF` next to the bond window |
| `Jk03` | 2 pads 0.5 mm at 1.1 mm pitch | | Differential probe: pin 1 `OUT`, pin 2 `REF` |
| `Rk01`, `Rk02` | 10 kΩ 0603 | fitted | DC taps to the monitor headers |
| `Rk03`, `Rk04` | 0 Ω 0603 | not fitted | Links to the SMA lines |
| `Ck03`, `Ck04` | 100 nF 0603 | fitted | DC blocks of the SMA lines |
| `Jk01`, `Jk02` | Molex 73251-1153 | fitted | Edge SMAs of `OUT` and `REF` |

The off-chip capacitor sets the IF bandwidth. The testbenches use 5 pF (−3 dB at 1.29 GHz), and the 2.7 pF assume about 2.3 pF of probe input, pads and trace. Adjust `Ck01` and `Ck02` once the probe is known.

Two readout modes:

- Differential probe on `Jk03` with the links out (default). It reads `OUT − REF` and loads each node only with the probe's input impedance.
- SMAs with `Rk03` and `Rk04` fitted, subtracted in the oscilloscope. `OUT` drives with about 25 Ω but `REF` with about 250 Ω, so the 50 Ω inputs cost 6.6 dB of `OUT − REF` at low IF and 4 dB at 2 GHz.

The SMA lines are grounded coplanar waveguides on `F.Cu` over `In1.Cu`, 0.18 mm wide with 0.15 mm gaps. They bend in tangent arcs of 1.1 to 1.5 mm radius. All other tracks bend in 45° corners.

The DC monitor headers carry the detector voltages through the 10 kΩ taps. Each sits in a bottom corner with its signal row above the `GND` row and pin 1 at the right end.

| Header | Pin 1 | Pin 3 | Pin 5 | Pin 7 |
| --- | --- | --- | --- | --- |
| `J4` (left) | `OUT3` | `REF3` | `REF1` | `OUT1` |
| `J5` (right) | `OUT2` | `REF2` | `REF4` | `OUT4` |

## Supply

| `JP1` | Source |
| --- | --- |
| 1-2 (default, bridged) | `VIN` of 3.3 to 5 V on the red jack `J1` (black `J3`), through the reverse polarity diode `D1` into the LP5907 LDO `U2` at 1.5 V |
| 2-3 | `VDD` straight from the yellow jack `J2` (black `J6`), 1.4 to 1.6 V, never above 1.6 V. Cut the 1-2 bridge first. |

`VDD` reaches the die pads 4 and 11 through the 0 Ω links `R1` and `R2`, which can be replaced by current shunts. Each pad has 100 pF and 1 nF C0G 0603 5.75 mm from the die centre, and 100 nF X7R 0603 and 1 µF X7R 0805 beside the link. The die draws 17.5 mA (4.36 mA per detector, simulated). The LDO sees 3.2 µF on its output, within the 10 µF limit of the LP5907.

## Assembly

Every passive is 0603 or 0805 except the eight 0402 off-chip capacitors next to the bond window, so the board can be soldered by hand. An 0603 there would sit further from the die with more loop inductance (about 1.2 nH against 0.7 nH), which moves its self-resonance to about 2.5 GHz and bends the IF response near 2 GHz. With the 0402 at 2.7 pF the response stays within 0.4 dB of the original 0201 design up to 2 GHz (lumped estimate). Solder all parts before the die is glued and bonded, and let the bonder operator check the clearance of the 0603 capacitors, which stand up to 0.9 mm tall about 4 mm from the bond fingers.

## Markings

- Layer marker in the LO corridor: `TOP` (`F.Cu`) and `2` (`In1.Cu`) are read from the top, `3` (`In2.Cu`) and `BOT` (`B.Cu`), mirrored, from the bottom. The copper text is 2.0 mm high, 1.7 mm wide, with 0.25 mm stroke. Each pair sits in rule areas that forbid only the pour (8.5 × 4.0 mm on the outer layer, 2.8 × 4.0 mm around each inner digit), under a mask window 0.1 mm inside the area, so a delivered board shows its layer order. The inner digits show through the laminate on the board, not in KiCad's render.
- Write-on field for the serial number: a filled 7.2 × 3.0 mm silkscreen rectangle under the bond test pad.
- Logos as filled silkscreen polygons in board-only footprints (no schematic symbol, not in the BOM or the position files): JKU 9.0 × 2.9 mm, ESD 6.5 × 5.9 mm, WEEE 7.0 × 9.9 mm.
- The WEEE logo is KiCad's stock artwork scaled to 7.0 mm width. Below that its 45° strokes are thinner than the 0.15 mm silkscreen line: a 0.15 mm opening removes 16 % of the 5.6 × 8 mm stock size and 0.3 % at 7.0 mm.

## Fabrication

The board fits both JLCPCB and Aisler on one rule set, so either fab can build it unchanged.

| Rule | Value |
| --- | --- |
| Track and space | 0.125 mm |
| Vias | 0.25 to 0.45 mm drill, 0.1 mm ring, 0.45 mm diameter or more (the board uses 0.3 mm in 0.6 mm) |
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
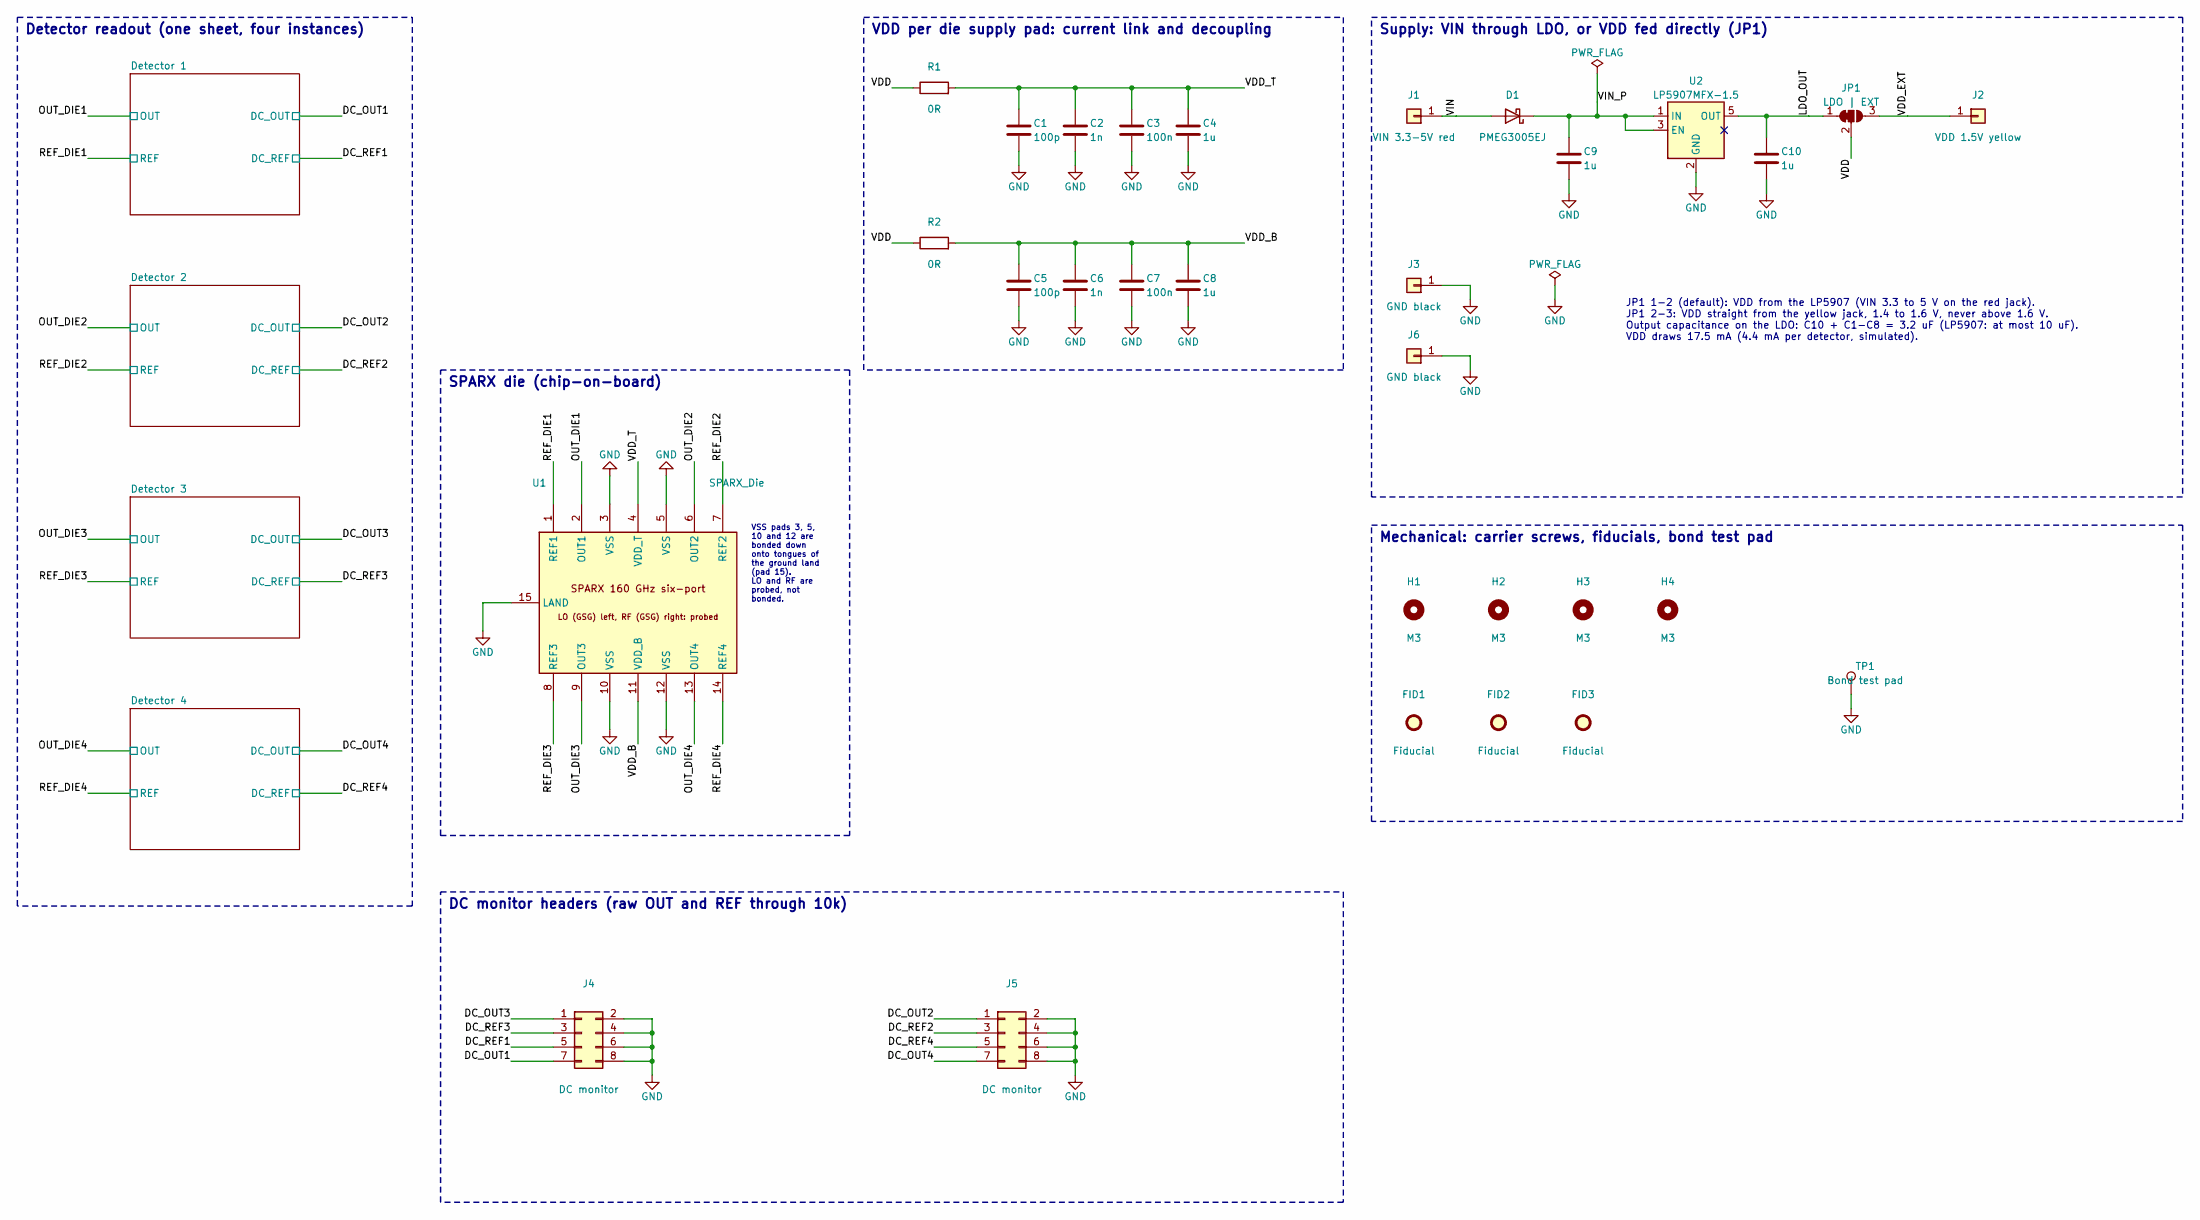
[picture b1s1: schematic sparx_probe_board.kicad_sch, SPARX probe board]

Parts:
C1, C5: 100p; C_0603_1608Metric
C2, C6: 1n; C_0603_1608Metric
C3, C7: 100n; C_0603_1608Metric
C4, C8, C9, C10: 1u; C_0805_2012Metric
D1: PMEG3005EJ; D_SOD-323F; MPN PMEG3005EJ
FID1, FID2, FID3: Fiducial; Fiducial_1mm_Mask2mm
H1, H2, H3, H4: M3; MountingHole_3.2mm_M3_DIN965
J1: VIN 3.3-5V red; TipJack_Cinch_105-075x_Horizontal_P10.16mm_Red; MPN 105-0752-001
J2: VDD 1.5V yellow; TipJack_Cinch_105-075x_Horizontal_P10.16mm_Yellow; MPN 105-0757-001
J3, J6: GND black; TipJack_Cinch_105-075x_Horizontal_P10.16mm_Black; MPN 105-0753-001
J4, J5: DC monitor; PinHeader_2x04_P2.54mm_Vertical
JP1: LDO | EXT; SolderJumper-3_P1.3mm_Bridged12_RoundedPad1.0x1.5mm
R1, R2: 0R; R_0603_1608Metric
TP1: Bond test pad; BondTestPad_5x5mm
U1: SPARX_Die; SPARX_Die_COB_1050x1350um; MPN SPARX (IHP SG13CMOS, March 2026 run)
U2: LP5907MFX-1.5; SOT-23-5; MPN LP5907MFX-1.5/NOPB

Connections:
/DC_OUT1: J4.7; also elsewhere on the board
/DC_OUT2: J5.1; also elsewhere on the board
/DC_OUT3: J4.1; also elsewhere on the board
/DC_OUT4: J5.7; also elsewhere on the board
/DC_REF1: J4.5; also elsewhere on the board
/DC_REF2: J5.3; also elsewhere on the board
/DC_REF3: J4.3; also elsewhere on the board
/DC_REF4: J5.5; also elsewhere on the board
/LDO_OUT: C10.1, JP1.1 (A), U2.5 (OUT)
/OUT_DIE1: U1.2 (OUT1); also elsewhere on the board
/OUT_DIE2: U1.6 (OUT2); also elsewhere on the board
/OUT_DIE3: U1.9 (OUT3); also elsewhere on the board
/OUT_DIE4: U1.13 (OUT4); also elsewhere on the board
/REF_DIE1: U1.1 (REF1); also elsewhere on the board
/REF_DIE2: U1.7 (REF2); also elsewhere on the board
/REF_DIE3: U1.8 (REF3); also elsewhere on the board
/REF_DIE4: U1.14 (REF4); also elsewhere on the board
/VDD: JP1.2 (C), R1.1, R2.1
/VDD_B: C5.1, C6.1, C7.1, C8.1, R2.2, U1.11 (VDD_B)
/VDD_EXT: J2.1, JP1.3 (B)
/VDD_T: C1.1, C2.1, C3.1, C4.1, R1.2, U1.4 (VDD_T)
/VIN: D1.2 (A), J1.1
/VIN_P: C9.1, D1.1 (K), U2.1 (IN), U2.3 (EN)
GND: C1.2, C2.2, C3.2, C4.2, C5.2, C6.2, C7.2, C8.2, C9.2, C10.2, J3.1, J4.2, J4.4, J4.6, J4.8, J5.2, J5.4, J5.6, J5.8, J6.1, TP1.1, U1.3 (VSS), U1.5 (VSS), U1.10 (VSS), U1.12 (VSS), U1.15 (LAND), U2.2 (GND); also elsewhere on the board

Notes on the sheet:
DC monitor headers (raw OUT and REF through 10k)
SPARX die (chip-on-board)
Detector readout (one sheet, four instances)
Supply: VIN through LDO, or VDD fed directly (JP1)
JP1 1-2 (default): VDD from the LP5907 (VIN 3.3 to 5 V on the red jack). JP1 2-3: VDD straight from the yellow jack, 1.4 to 1.6 V, never above 1.6 V. Output capacitance on the LDO: C10 + C1-C8 = 3.2 uF (LP5907: at most 10 uF). VDD draws 17.5 mA (4.4 mA per detector, simulated).
Mechanical: carrier screws, fiducials, bond test pad
VSS pads 3, 5, 10 and 12 are bonded down onto tongues of the ground land (pad 15). LO and RF are probed, not bonded.
VDD per die supply pad: current link and decoupling

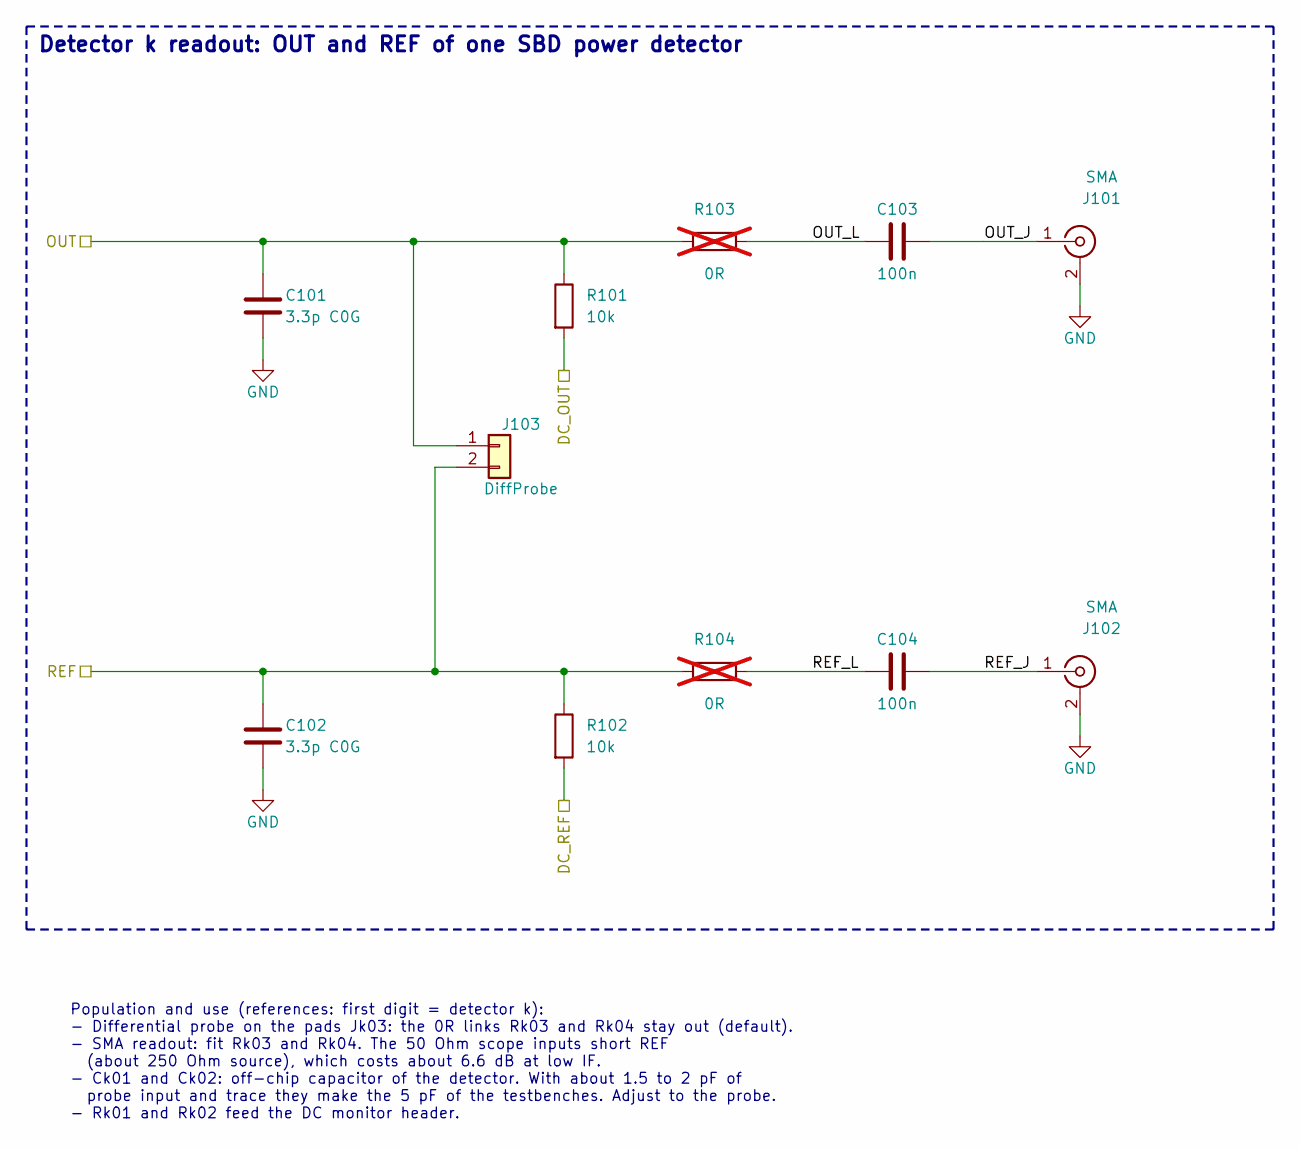
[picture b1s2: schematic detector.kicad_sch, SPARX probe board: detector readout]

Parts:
C101, C102: 3.3p C0G; C_0201_0603Metric; Tolerance 0.1pF; Voltage 50V
C103, C104: 100n; C_0402_1005Metric
J101, J102: SMA; SMA_Molex_73251-1153_EdgeLaunch; MPN 73251-1153
J103: DiffProbe; DiffProbe_Pads_2x0.5mm_P1.1mm
R101, R102: 10k; R_0402_1005Metric
R103, R104: 0R; R_0402_1005Metric; not fitted

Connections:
/DC_OUT1: R101.2; also elsewhere on the board
/DC_REF1: R102.2; also elsewhere on the board
/Detector 1/OUT_J: C103.2, J101.1 (In)
/Detector 1/OUT_L: C103.1, R103.2
/Detector 1/REF_J: C104.2, J102.1 (In)
/Detector 1/REF_L: C104.1, R104.2
/OUT_DIE1: C101.1, J103.1, R101.1, R103.1; also elsewhere on the board
/REF_DIE1: C102.1, J103.2, R102.1, R104.1; also elsewhere on the board
GND: C101.2, C102.2, J101.2 (Ext), J102.2 (Ext); also elsewhere on the board

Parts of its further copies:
C203, C204, C303, C304, C403, C404: 100n; C_0402_1005Metric
J201, J202, J301, J302, J401, J402: SMA; SMA_Molex_73251-1153_EdgeLaunch; MPN 73251-1153
J203, J303, J403: DiffProbe; DiffProbe_Pads_2x0.5mm_P1.1mm
R201, R202, R301, R302, R401, R402: 10k; R_0402_1005Metric
R203, R204, R303, R304, R403, R404: 0R; R_0402_1005Metric; not fitted

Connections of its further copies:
/DC_OUT2: R201.2; also elsewhere on the board
/DC_OUT3: R301.2; also elsewhere on the board
/DC_OUT4: R401.2; also elsewhere on the board
/DC_REF2: R202.2; also elsewhere on the board
/DC_REF3: R302.2; also elsewhere on the board
/DC_REF4: R402.2; also elsewhere on the board
/Detector 2/OUT_J: C203.2, J201.1 (In)
/Detector 2/OUT_L: C203.1, R203.2
/Detector 2/REF_J: C204.2, J202.1 (In)
/Detector 2/REF_L: C204.1, R204.2
/Detector 3/OUT_J: C303.2, J301.1 (In)
/Detector 3/OUT_L: C303.1, R303.2
/Detector 3/REF_J: C304.2, J302.1 (In)
/Detector 3/REF_L: C304.1, R304.2
/Detector 4/OUT_J: C403.2, J401.1 (In)
/Detector 4/OUT_L: C403.1, R403.2
/Detector 4/REF_J: C404.2, J402.1 (In)
/Detector 4/REF_L: C404.1, R404.2
/OUT_DIE2: J203.1, R201.1, R203.1; also elsewhere on the board
/OUT_DIE3: J303.1, R301.1, R303.1; also elsewhere on the board
/OUT_DIE4: J403.1, R401.1, R403.1; also elsewhere on the board
/REF_DIE2: J203.2, R202.1, R204.1; also elsewhere on the board
/REF_DIE3: J303.2, R302.1, R304.1; also elsewhere on the board
/REF_DIE4: J403.2, R402.1, R404.1; also elsewhere on the board
GND: J201.2 (Ext), J202.2 (Ext), J301.2 (Ext), J302.2 (Ext), J401.2 (Ext), J402.2 (Ext); also elsewhere on the board

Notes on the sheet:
Population and use (references: first digit = detector k): - Differential probe on the pads Jk03: the 0R links Rk03 and Rk04 stay out (default). - SMA readout: fit Rk03 and Rk04. The 50 Ohm scope inputs short REF (about 250 Ohm source), which costs about 6.6 dB at low IF. - Ck01 and Ck02: off-chip 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
Detector k readout: OUT and REF of one SBD power detector

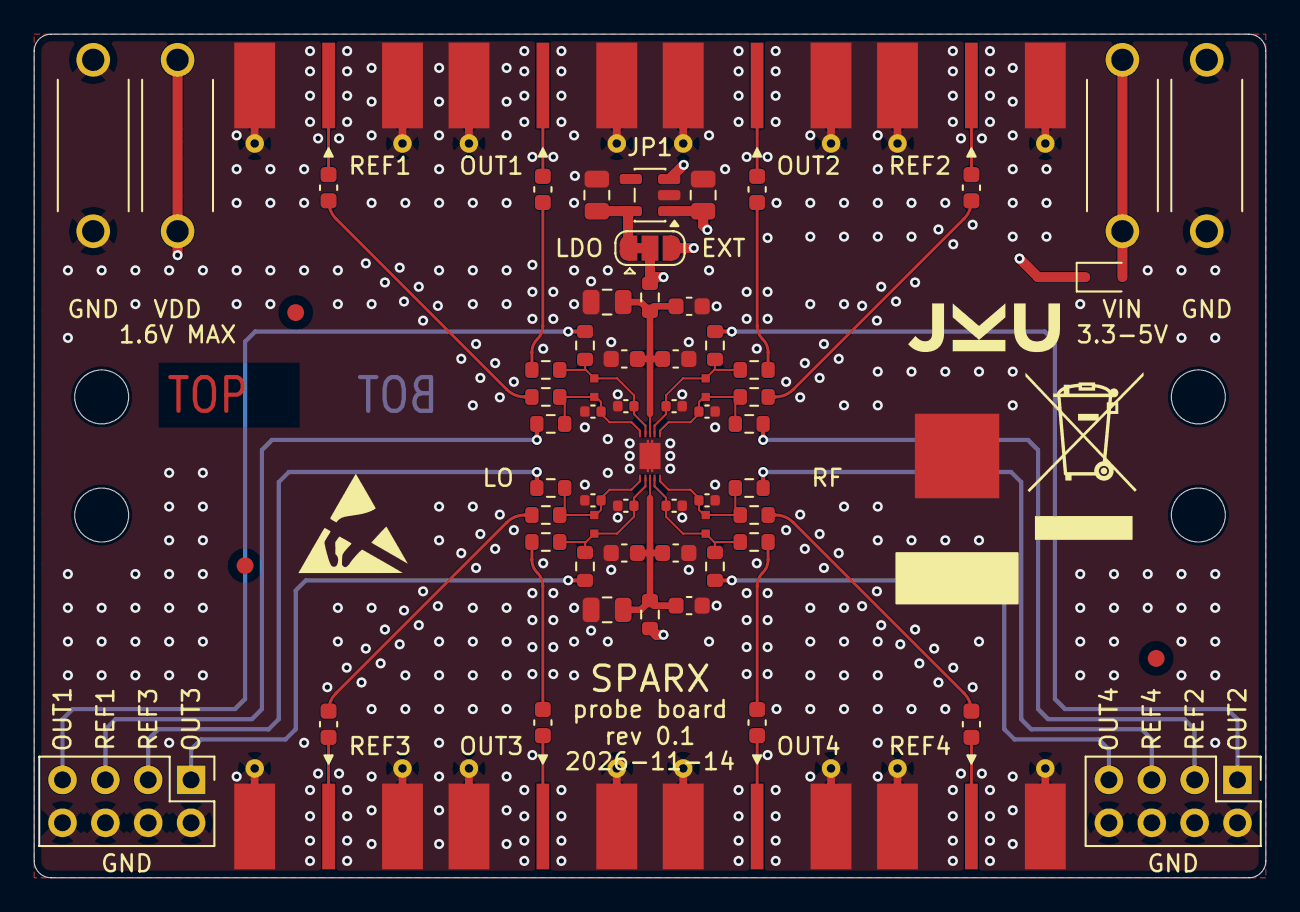
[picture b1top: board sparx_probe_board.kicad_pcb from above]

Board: 4 copper layers, 73.0 x 50.0 mm, 77 parts (0 on the bottom side), 40 nets.

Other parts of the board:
C201, C202, C301, C302, C401, C402: 2.7p C0G; C_0402_1005Metric
LOGO1: Logo_JKU_9.0x2.9mm
LOGO2: Logo_ESD_6.5x5.9mm
LOGO3: Logo_WEEE_7.0x9.9mm

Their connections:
/OUT_DIE2: C201.1; also elsewhere on the board
/OUT_DIE3: C301.1; also elsewhere on the board
/OUT_DIE4: C401.1; also elsewhere on the board
/REF_DIE2: C202.1; also elsewhere on the board
/REF_DIE3: C302.1; also elsewhere on the board
/REF_DIE4: C402.1; also elsewhere on the board
GND: C201.2, C202.2, C301.2, C302.2, C401.2, C402.2; also elsewhere on the board

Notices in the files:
README.md:
License:
Licensed under the **Solderpad Hardware License v2.1**, see [`LICENSE`](LICENSE).
License: Solderpad Hardware License v2.1
Please cite the paper and the repository:
pcb/detector.kicad_sch:
SPDX-FileCopyrightText: 2026 The SPARX Team
SPDX-License-Identifier: Apache-2.0 WITH SHL-2.1
